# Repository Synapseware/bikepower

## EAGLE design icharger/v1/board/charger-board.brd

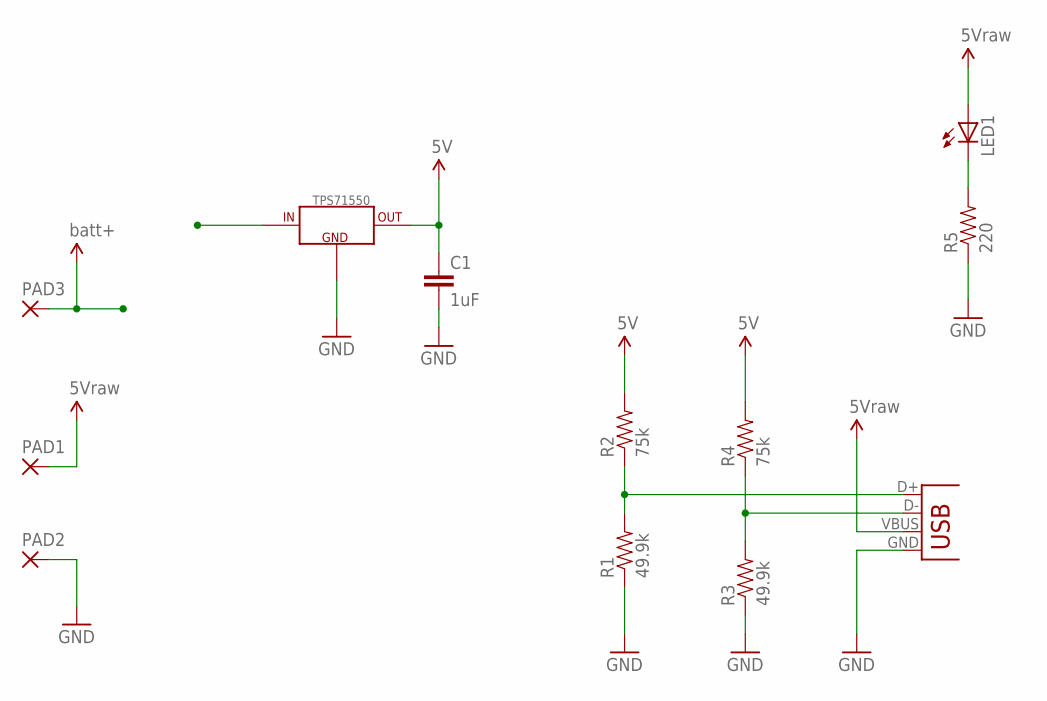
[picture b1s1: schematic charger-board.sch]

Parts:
C1: 1uF; 0805
JP1: USB-A-S
LED1: LED0603; LED-0603
PAD1, PAD2, PAD3: WIREPAD2,54/0,8; 2,54/0,8
R1, R3: 49.9k; 0603-RES
R2, R4: 75k; 0603-RES
R5: 220; 0603-RES
TPS71550: TPS715XX; SC70-5

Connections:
5V: C1.1, R2.2, R4.2, TPS71550.5 (OUT)
5VRAW: JP1.VBUS, LED1.A, PAD1.1
BATT+: PAD3.1, TPS71550.4 (IN)
GND: C1.2, JP1.GND, PAD2.1, R1.1, R3.1, R5.1, TPS71550.2 (GND)
unnamed: LED1.C, R5.2
unnamed: JP1.D-, R3.2, R4.1
unnamed: JP1.D+, R1.2, R2.1

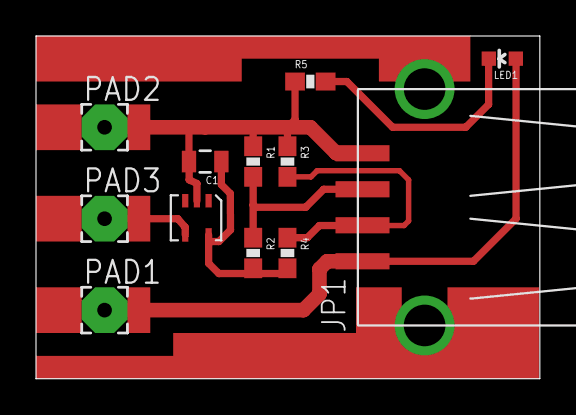
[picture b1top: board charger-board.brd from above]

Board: 2 copper layers, 28.0 x 19.0 mm, 12 parts (0 on the bottom side), 7 nets.

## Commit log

2014-06-19 migrating project

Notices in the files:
parts and their libraries:
SparkFun-Passives: Licensing: CC v3.0 Share-Alike You are welcome to use this library for commercial purposes.
